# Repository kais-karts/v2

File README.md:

# 🏎️ Kai-Karts _V2_
## Description
This time it's gonna work.

## Installation
Refer to the `README.md` for the relevant sub-systems.
TODO: installation on RPi + Wiring

## Running
On the Go-Kart's RPi, run `main.py`. That's it.

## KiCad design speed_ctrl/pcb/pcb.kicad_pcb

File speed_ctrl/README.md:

# Speed Ctrl
## Description
This is the hardware (+ minimal software) to variably divide the voltage going from the Go-Kart's pedal to the motor speed controller.

## Setup
### Hardware
Connect:
GPIO 27 -> INC\
GPIO 22 -> UD

### Software
Just import the module and call set_speed_multiplier() whenever you wish to change the multiplier. **Note multiplier will start at 0 upon initialization as of now, thus car will not move until you change the multiplier**. See set_speed_multiplier() docstring for a description of the functions inputs and outputs.

## Development Notes
3/29/2025 \
Completed all the TODOs, all thats left is to test and order PCBs

3/19/2025 \
Proof of concept works, whats left to do:
- make it work without needing to reset every call (reset should just be last resort when software not in sync with hardware)
- make number of taps a parameter (dont hard code 100)
- make the proof of concept circuit have buffered input and output with TL082 (input from external power supply, output is wiper to be probed)
- label lines on proof of concept

3/16/2025 \
Im thinking Vh/Rh, VCC  connect to 5v. Vl/Rl, VSS connected to GND. Also all other pins defined in constants for now but just GPIOs.

Speed controller breakouts arrived, watching [tutorial](https://www.youtube.com/watch?v=Zy50ZGSJLqM) introduces concern of potential amplifier needed to boost power of signal (10mW max power output of X9103). Should have some fail-fast protections in whatever I write (cause error whenever trying to be used when uninitialized, etc). Also will need to make a setup that is persistent across reboots -- no one wants to have to recalibrate cause the program power cycled (aka write to file before returning from function, read state from file)

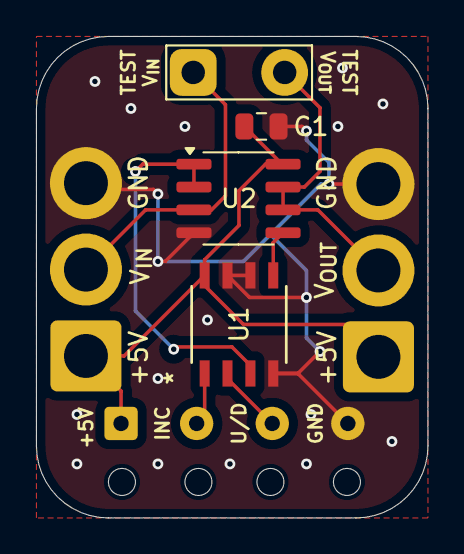
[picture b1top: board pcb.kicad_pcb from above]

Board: 2 copper layers, 21.8 x 26.8 mm, 11 parts (0 on the bottom side), 8 nets.

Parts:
+5V: MountingHole; MountingHole_1.5mm
C1: 0.1µF; C_0805_2012Metric
GND: MountingHole; MountingHole_1.5mm
INC: MountingHole; MountingHole_1.5mm
J3: Pi Connections; SolderWire-0.25sqmm_1x04_P4.2mm_D0.65mm_OD1.7mm
TP1: Test Point; TestPoint_2Pads_Pitch5.08mm_Drill1.3mm
U1: X9C103SZT1; X9C103SZT1_REN
U2: TL082; SOIC-8_3.9x4.9mm_P1.27mm
U/D: MountingHole; MountingHole_1.5mm
V_{IN}: Pigtail In; SolderWire-0.75sqmm_1x03_P4.8mm_D1.25mm_OD2.3mm
V_{OUT}: Pigtail Out; SolderWire-0.75sqmm_1x03_P4.8mm_D1.25mm_OD2.3mm

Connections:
+5V: C1.1, J3.1, U1.8 (VCC), U2.8 (V+), V_{IN}.1, V_{OUT}.1
GND: C1.2, J3.4, U1.4 (VSS), U1.6 (RL/VL), U1.7 (*CS), U2.4 (V-), V_{IN}.3, V_{OUT}.3
INC: J3.2, U1.1 (*INC)
unnamed: U1.3 (VH/RH), U2.1, U2.2 (-)
unnamed: U1.5 (VW/RW), U2.5 (+)
U/D: J3.3, U1.2 (U/*D)
V_{IN}: TP1.1, U2.3 (+), V_{IN}.2
V_{OUT}: TP1.2, U2.6 (-), U2.7, V_{OUT}.2

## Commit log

2025-03-10 Setup sub-folders and add initial code
2025-03-10 Add top-level readme
2025-03-16 first pass at game logic (receiving end)
2025-03-16 organized files
2025-03-17 Move some stuff around for integration
2025-03-17 dataget test
2025-03-17 Cleanup `pyc` junk
2025-03-17 Add more skeleton code
2025-03-17 rename
2025-03-19 proven concept
2025-03-19 Update README.md and added TODO
2025-03-20 map displays and shuffle works
2025-03-20 to_do + skeleton functions:
2025-03-20 added basic radio 2-way comms
2025-03-20 added mystery boxes on ui
2025-03-20 Added backbone for ranking update
2025-03-21 Create Map object
2025-03-21 added plotter
2025-03-21 added plotter again
2025-03-21 Implemented item within GoKart - ability to be hit with item and pickup
2025-03-21 Update to do
2025-03-30 untested completed TODOs
2025-03-30 Add speed control PCB
2025-03-31 update item effect name change
2025-03-31 organzied items better + impl item attacks
2025-03-31 updated to do
2025-03-31 button logic + moved kart update to main update loop
2025-03-31 update to_do
2025-03-31 small bug fix + docstring updates
2025-03-31 fix small bug, changed numtaps to 32
2025-04-02 added api
2025-04-02 fixed gitignore
2025-04-05 refactor
2025-04-05 reorg files
2025-04-05 clean attacked logic
2025-04-05 Game logic -> UI communication
2025-04-07 live gps draw
2025-04-10 Update PCB
2025-04-10 Fix gitignore
2025-04-10 Fix import paths (mostly)
2025-04-10 Made work more with our defined packet
2025-04-11 Consolidate UI API
2025-04-11 Use `Item` struct
2025-04-11 updated gitignore
2025-04-11 a few ui things
2025-04-11 add new `Item`
2025-04-11 charachters
2025-04-11 corrected kart ui class but ui doesnt load
2025-04-11 new ui structure (tested)
2025-04-11 fixed bugs. Tested with api
2025-04-11 Added frame checking in serial comms
2025-04-14 it works perfectly from 0v to 4.8v, complete success
2025-04-17 Fixed bugs and tested packet comms
